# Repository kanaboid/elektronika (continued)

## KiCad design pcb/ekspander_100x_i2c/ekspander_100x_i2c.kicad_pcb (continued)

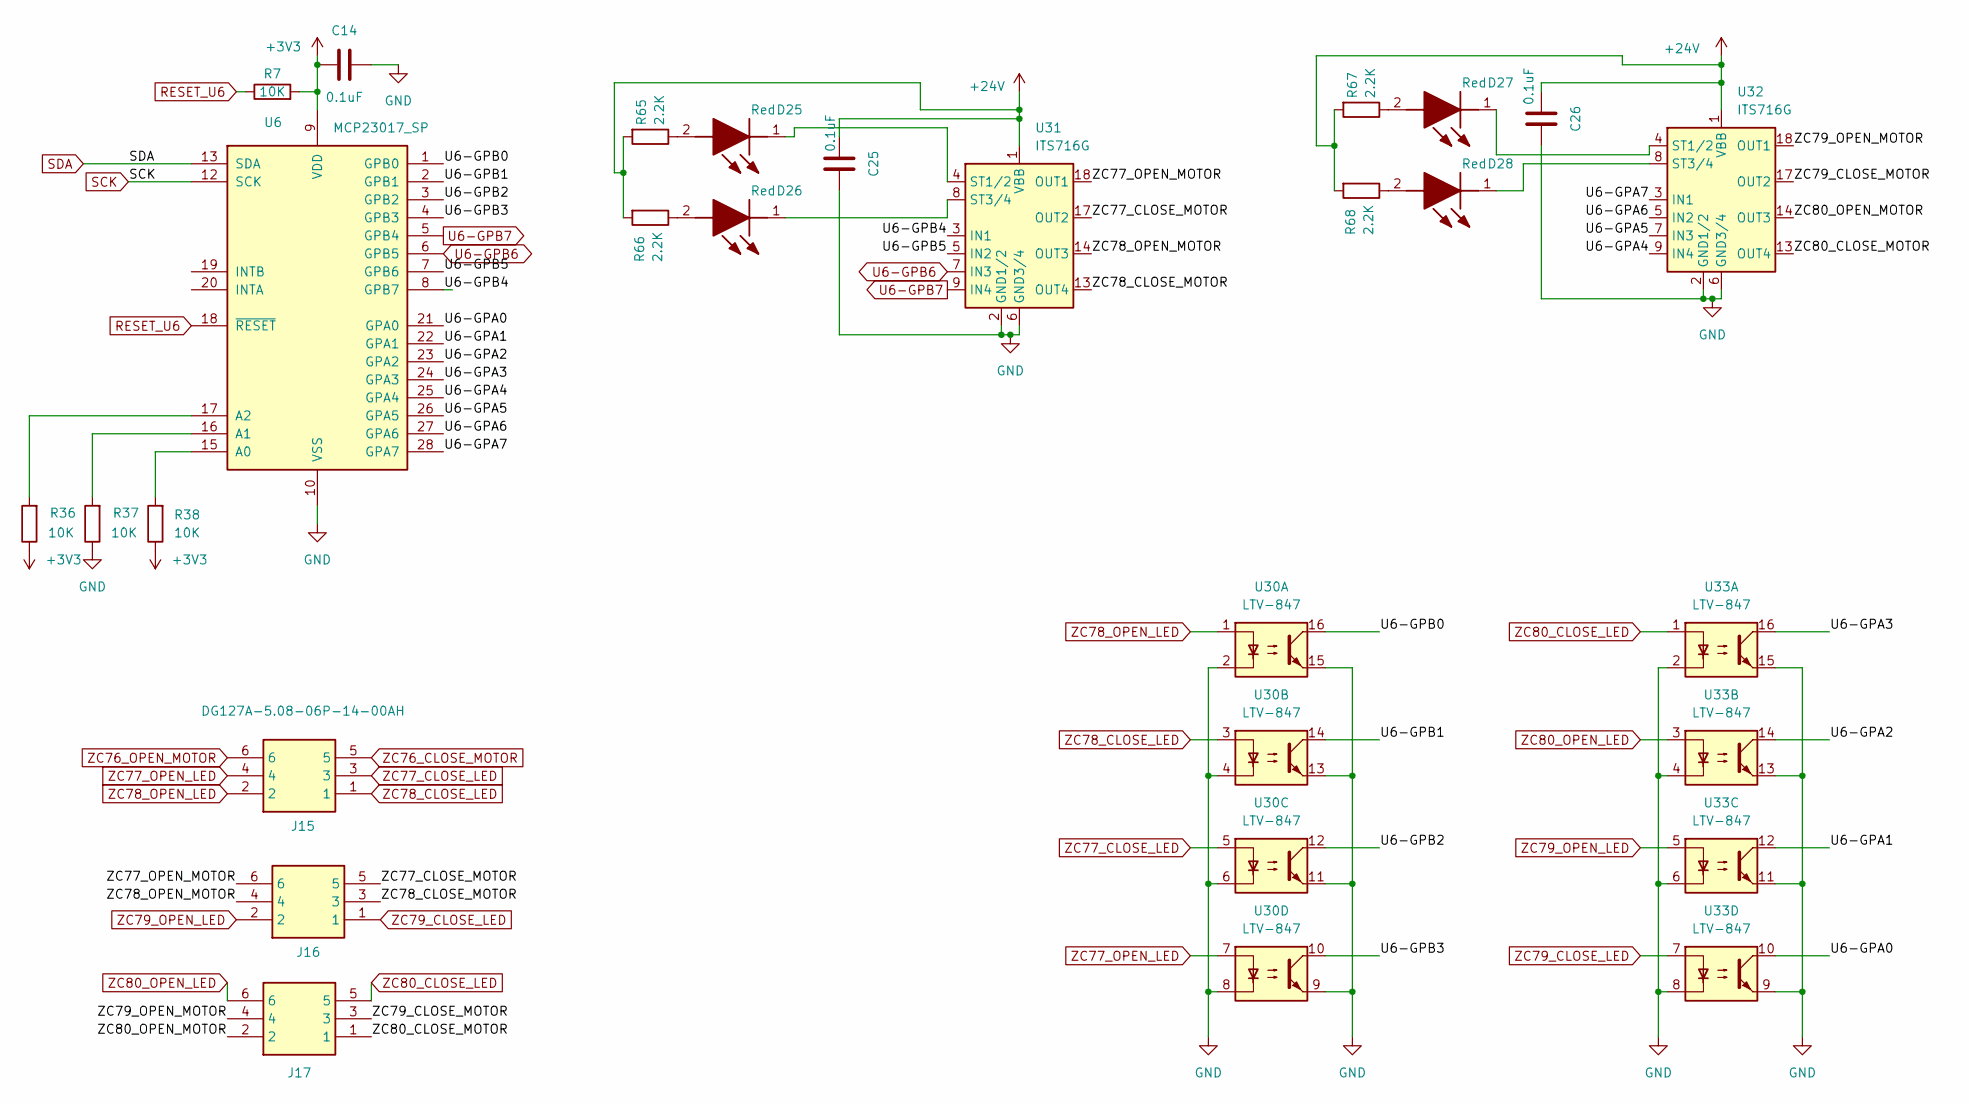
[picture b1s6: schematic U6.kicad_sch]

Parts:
C14, C25, C26: 0.1uF; C_0805_2012Metric_Pad1.18x1.45mm_HandSolder
D25, D26, D27, D28: Red; LEDC2012X120N; Manufacturer_Part_Number LTST-C170KRKT; Mouser Part Number 859-LTST-C170KRKT
J15, J16, J17: DG127A-5.08-06P-14-00AH; DG127A50806P1400AH; Manufacturer_Part_Number DG127A-5.08-06P-14-00AH
R7, R36, R37, R38: 10K; R_0805_2012Metric_Pad1.20x1.40mm_HandSolder
R65, R66, R67, R68: 2.2K; R_0805_2012Metric_Pad1.20x1.40mm_HandSolder
U6: MCP23017_SP; DIP-28_W7.62mm
U30, U33: LTV-847; DIP-16_W7.62mm
U31, U32: ITS716G; SOIC-20W_7.5x12.8mm_P1.27mm

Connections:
+3V3: C14.1, R7.2, R36.1, R38.1, U6.9 (VDD); also elsewhere on the board
+24V: C25.1, C26.1, R65.2, R66.2, R67.2, R68.2, U31.1 (VBB), U31.10 (VBB), U31.11 (VBB), U31.12 (VBB), U31.15 (VBB), U31.16 (VBB), U31.19 (VBB), U31.20 (VBB), U32.1 (VBB), U32.10 (VBB), U32.11 (VBB), U32.12 (VBB), U32.15 (VBB), U32.16 (VBB), U32.19 (VBB), U32.20 (VBB); also elsewhere on the board
/U6/U6-GPA0: U6.21 (GPA0), U33.10
/U6/U6-GPA1: U6.22 (GPA1), U33.12
/U6/U6-GPA2: U6.23 (GPA2), U33.14
/U6/U6-GPA3: U6.24 (GPA3), U33.16
/U6/U6-GPA4: U6.25 (GPA4), U32.9 (IN4)
/U6/U6-GPA5: U6.26 (GPA5), U32.7 (IN3)
/U6/U6-GPA6: U6.27 (GPA6), U32.5 (IN2)
/U6/U6-GPA7: U6.28 (GPA7), U32.3 (IN1)
/U6/U6-GPB0: U6.1 (GPB0), U30.16
/U6/U6-GPB1: U6.2 (GPB1), U30.14
/U6/U6-GPB2: U6.3 (GPB2), U30.12
/U6/U6-GPB3: U6.4 (GPB3), U30.10
/U6/U6-GPB4: U6.8 (GPB7), U31.3 (IN1)
/U6/U6-GPB5: U6.7 (GPB6), U31.5 (IN2)
/U6/ZC77_CLOSE_MOTOR: J16.5, U31.17 (OUT2)
/U6/ZC77_OPEN_MOTOR: J16.6, U31.18 (OUT1)
/U6/ZC78_CLOSE_MOTOR: J16.3, U31.13 (OUT4)
/U6/ZC78_OPEN_MOTOR: J16.4, U31.14 (OUT3)
/U6/ZC79_CLOSE_MOTOR: J17.3, U32.17 (OUT2)
/U6/ZC79_OPEN_MOTOR: J17.4, U32.18 (OUT1)
/U6/ZC80_CLOSE_MOTOR: J17.1, U32.13 (OUT4)
/U6/ZC80_OPEN_MOTOR: J17.2, U32.14 (OUT3)
GND: C14.2, C25.2, C26.2, R37.1, U6.10 (VSS), U30.2, U30.4, U30.6, U30.8, U30.9, U30.11, U30.13, U30.15, U31.2 (GND1/2), U31.6 (GND3/4), U32.2 (GND1/2), U32.6 (GND3/4), U33.2, U33.4, U33.6, U33.8, U33.9, U33.11, U33.13, U33.15; also elsewhere on the board
unnamed: D25.2 (A), R65.1
unnamed: D25.1 (K), U31.4 (ST1/2)
unnamed: D26.2 (A), R66.1
unnamed: D26.1 (K), U31.8 (ST3/4)
unnamed: D27.2 (A), R67.1
unnamed: D27.1 (K), U32.4 (ST1/2)
unnamed: D28.2 (A), R68.1
unnamed: D28.1 (K), U32.8 (ST3/4)
unnamed: R38.2, U6.15 (A0)
unnamed: R37.2, U6.16 (A1)
unnamed: R36.2, U6.17 (A2)
RESET_U6: R7.1, U6.18 (~RESET); also elsewhere on the board
SCK: U6.12 (SCK); also elsewhere on the board
SDA: U6.13 (SDA); also elsewhere on the board
U6-GPB6: U6.6 (GPB5), U31.7 (IN3)
U6-GPB7: U6.5 (GPB4), U31.9 (IN4)
ZC76_CLOSE_MOTOR: J15.5; also elsewhere on the board
ZC76_OPEN_MOTOR: J15.6; also elsewhere on the board
ZC77_CLOSE_LED: J15.3, U30.5
ZC77_OPEN_LED: J15.4, U30.7
ZC78_CLOSE_LED: J15.1, U30.3
ZC78_OPEN_LED: J15.2, U30.1
ZC79_CLOSE_LED: J16.1, U33.7
ZC79_OPEN_LED: J16.2, U33.5
ZC80_CLOSE_LED: J17.5, U33.1
ZC80_OPEN_LED: J17.6, U33.3

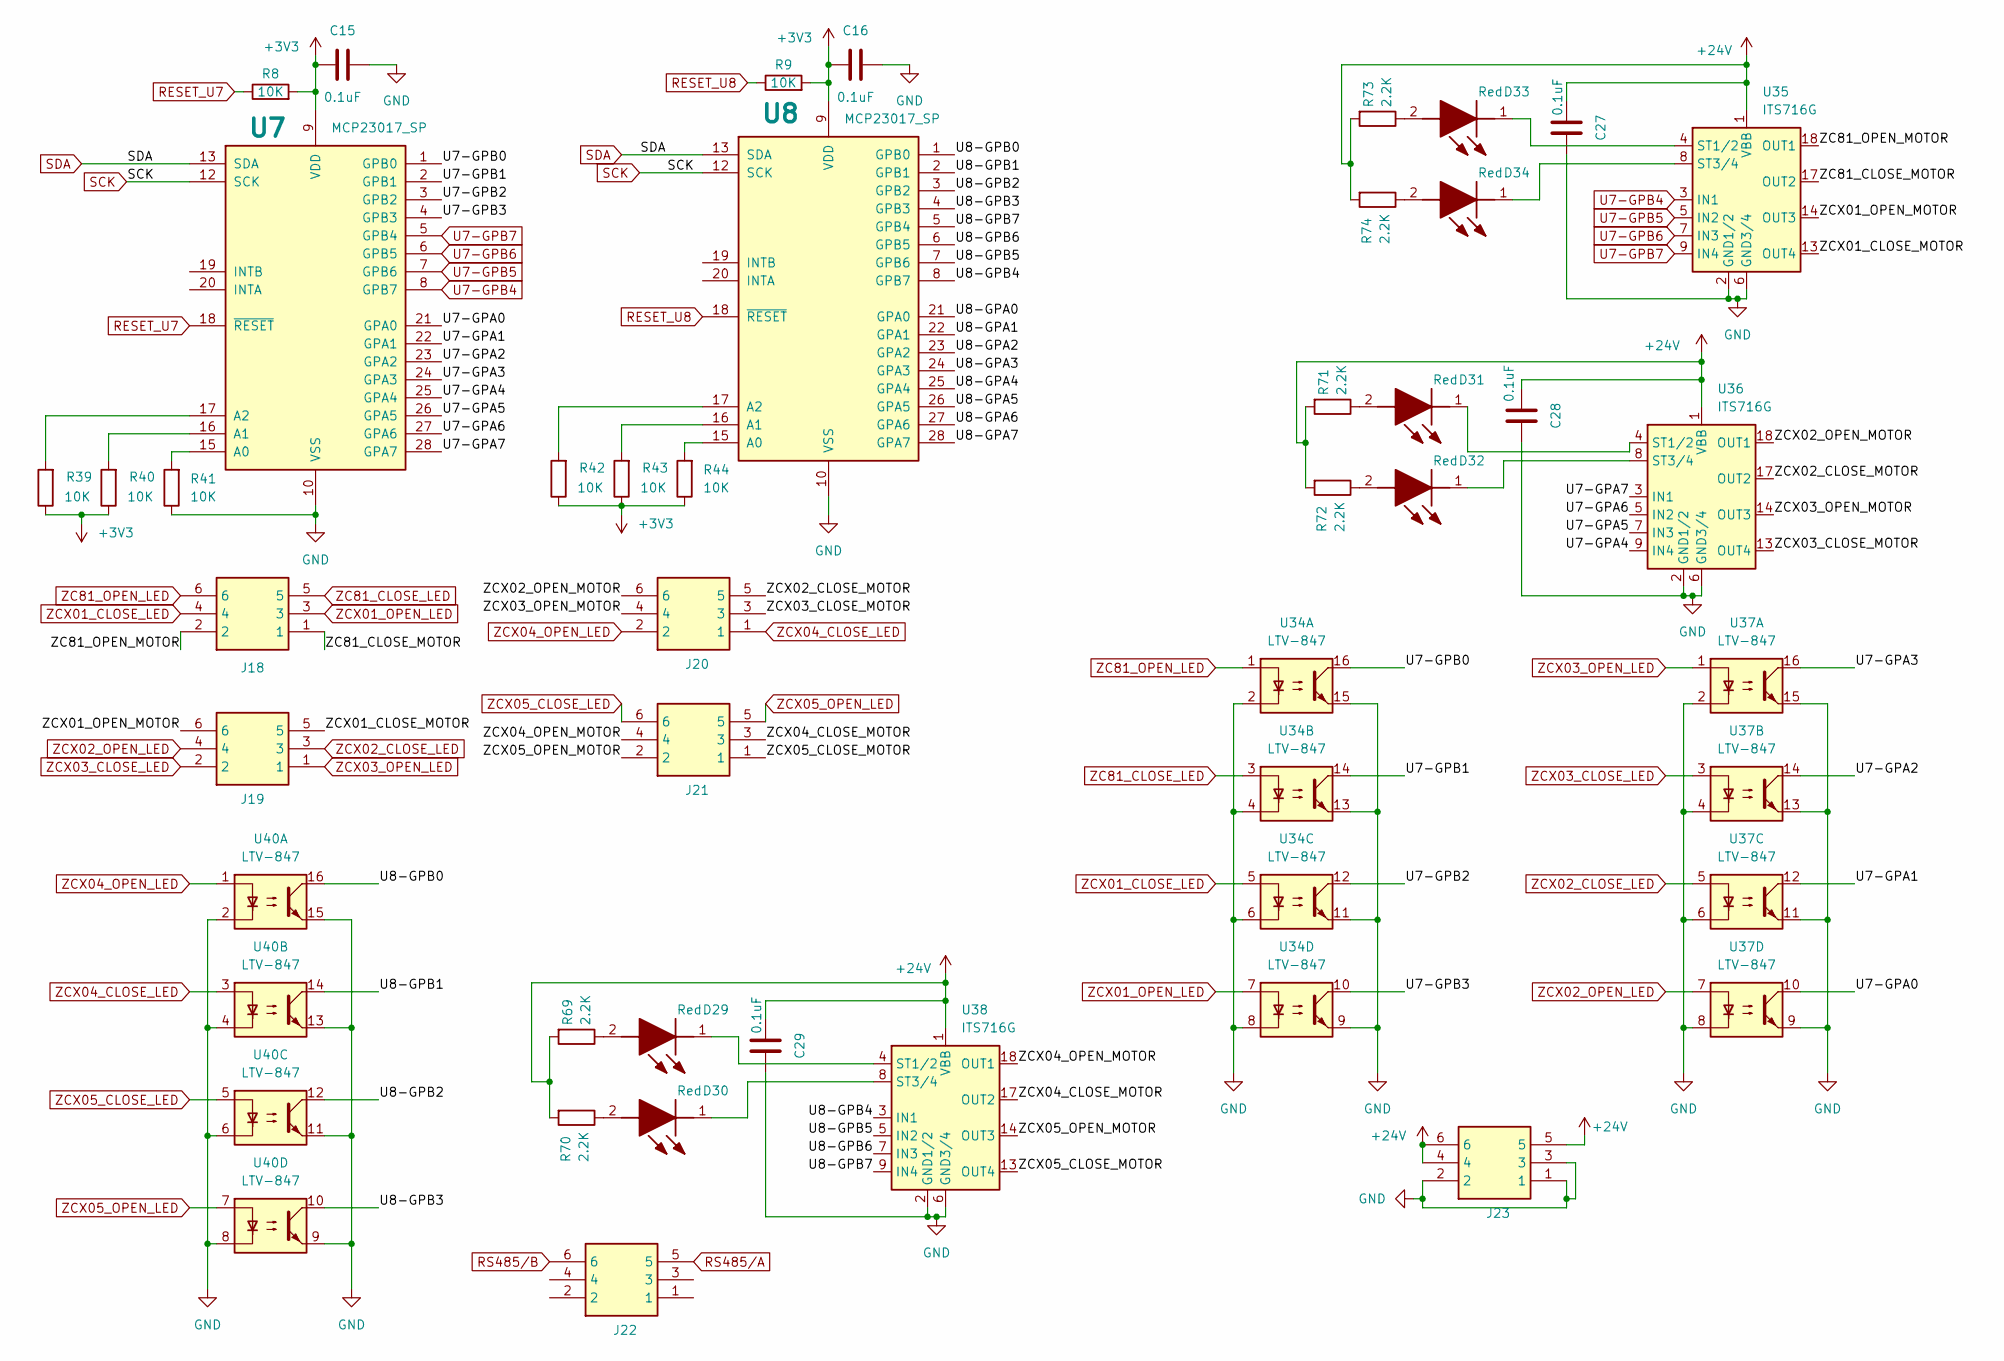
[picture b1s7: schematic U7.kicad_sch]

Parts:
C15, C16, C27, C28, C29: 0.1uF; C_0805_2012Metric_Pad1.18x1.45mm_HandSolder
D29, D30, D31, D32, D33, D34: Red; LEDC2012X120N; Manufacturer_Part_Number LTST-C170KRKT; Mouser Part Number 859-LTST-C170KRKT
J18, J19, J20, J21, J22, J23: DG127A-5.08-06P-14-00AH; DG127A50806P1400AH; Manufacturer_Part_Number DG127A-5.08-06P-14-00AH
R8, R9, R39, R40, R41, R42, R43, R44: 10K; R_0805_2012Metric_Pad1.20x1.40mm_HandSolder
R69, R70, R71, R72, R73, R74: 2.2K; R_0805_2012Metric_Pad1.20x1.40mm_HandSolder
U7, U8: MCP23017_SP; DIP-28_W7.62mm
U34, U37, U40: LTV-847; DIP-16_W7.62mm
U35, U36, U38: ITS716G; SOIC-20W_7.5x12.8mm_P1.27mm

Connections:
+3V3: C15.1, C16.1, R8.2, R9.2, R39.1, R40.1, R42.1, R43.1, R44.1, U7.9 (VDD), U8.9 (VDD); also elsewhere on the board
+24V: C27.1, C28.1, C29.1, J23.4, J23.5, J23.6, R69.2, R70.2, R71.2, R72.2, R73.2, R74.2, U35.1 (VBB), U35.10 (VBB), U35.11 (VBB), U35.12 (VBB), U35.15 (VBB), U35.16 (VBB), U35.19 (VBB), U35.20 (VBB), U36.1 (VBB), U36.10 (VBB), U36.11 (VBB), U36.12 (VBB), U36.15 (VBB), U36.16 (VBB), U36.19 (VBB), U36.20 (VBB), U38.1 (VBB), U38.10 (VBB), U38.11 (VBB), U38.12 (VBB), U38.15 (VBB), U38.16 (VBB), U38.19 (VBB), U38.20 (VBB); also elsewhere on the board
/U7 - U8/U7-GPA0: U7.21 (GPA0), U37.10
/U7 - U8/U7-GPA1: U7.22 (GPA1), U37.12
/U7 - U8/U7-GPA2: U7.23 (GPA2), U37.14
/U7 - U8/U7-GPA3: U7.24 (GPA3), U37.16
/U7 - U8/U7-GPA4: U7.25 (GPA4), U36.9 (IN4)
/U7 - U8/U7-GPA5: U7.26 (GPA5), U36.7 (IN3)
/U7 - U8/U7-GPA6: U7.27 (GPA6), U36.5 (IN2)
/U7 - U8/U7-GPA7: U7.28 (GPA7), U36.3 (IN1)
/U7 - U8/U7-GPB0: U7.1 (GPB0), U34.16
/U7 - U8/U7-GPB1: U7.2 (GPB1), U34.14
/U7 - U8/U7-GPB2: U7.3 (GPB2), U34.12
/U7 - U8/U7-GPB3: U7.4 (GPB3), U34.10
/U7 - U8/U8-GPA0: U8.21 (GPA0)
/U7 - U8/U8-GPA1: U8.22 (GPA1)
/U7 - U8/U8-GPA2: U8.23 (GPA2)
/U7 - U8/U8-GPA3: U8.24 (GPA3)
/U7 - U8/U8-GPA4: U8.25 (GPA4)
/U7 - U8/U8-GPA5: U8.26 (GPA5)
/U7 - U8/U8-GPA6: U8.27 (GPA6)
/U7 - U8/U8-GPA7: U8.28 (GPA7)
/U7 - U8/U8-GPB0: U8.1 (GPB0), U40.16
/U7 - U8/U8-GPB1: U8.2 (GPB1), U40.14
/U7 - U8/U8-GPB2: U8.3 (GPB2), U40.12
/U7 - U8/U8-GPB3: U8.4 (GPB3), U40.10
/U7 - U8/U8-GPB4: U8.8 (GPB7), U38.3 (IN1)
/U7 - U8/U8-GPB5: U8.7 (GPB6), U38.5 (IN2)
/U7 - U8/U8-GPB6: U8.6 (GPB5), U38.7 (IN3)
/U7 - U8/U8-GPB7: U8.5 (GPB4), U38.9 (IN4)
/U7 - U8/ZC81_CLOSE_MOTOR: J18.1, U35.17 (OUT2)
/U7 - U8/ZC81_OPEN_MOTOR: J18.2, U35.18 (OUT1)
/U7 - U8/ZCX01_CLOSE_MOTOR: J19.5, U35.13 (OUT4)
/U7 - U8/ZCX01_OPEN_MOTOR: J19.6, U35.14 (OUT3)
/U7 - U8/ZCX02_CLOSE_MOTOR: J20.5, U36.17 (OUT2)
/U7 - U8/ZCX02_OPEN_MOTOR: J20.6, U36.18 (OUT1)
/U7 - U8/ZCX03_CLOSE_MOTOR: J20.3, U36.13 (OUT4)
/U7 - U8/ZCX03_OPEN_MOTOR: J20.4, U36.14 (OUT3)
/U7 - U8/ZCX04_CLOSE_MOTOR: J21.3, U38.17 (OUT2)
/U7 - U8/ZCX04_OPEN_MOTOR: J21.4, U38.18 (OUT1)
/U7 - U8/ZCX05_CLOSE_MOTOR: J21.1, U38.13 (OUT4)
/U7 - U8/ZCX05_OPEN_MOTOR: J21.2, U38.14 (OUT3)
GND: C15.2, C16.2, C27.2, C28.2, C29.2, J23.1, J23.2, J23.3, R41.1, U7.10 (VSS), U8.10 (VSS), U34.2, U34.4, U34.6, U34.8, U34.9, U34.11, U34.13, U34.15, U35.2 (GND1/2), U35.6 (GND3/4), U36.2 (GND1/2), U36.6 (GND3/4), U37.2, U37.4, U37.6, U37.8, U37.9, U37.11, U37.13, U37.15, U38.2 (GND1/2), U38.6 (GND3/4), U40.2, U40.4, U40.6, U40.8, U40.9, U40.11, U40.13, U40.15; also elsewhere on the board
unnamed: D29.2 (A), R69.1
unnamed: D29.1 (K), U38.4 (ST1/2)
unnamed: D30.2 (A), R70.1
unnamed: D30.1 (K), U38.8 (ST3/4)
unnamed: D31.2 (A), R71.1
unnamed: D31.1 (K), U36.4 (ST1/2)
unnamed: D32.2 (A), R72.1
unnamed: D32.1 (K), U36.8 (ST3/4)
unnamed: D33.2 (A), R73.1
unnamed: D33.1 (K), U35.4 (ST1/2)
unnamed: D34.2 (A), R74.1
unnamed: D34.1 (K), U35.8 (ST3/4)
unnamed: R41.2, U7.15 (A0)
unnamed: R40.2, U7.16 (A1)
unnamed: R39.2, U7.17 (A2)
unnamed: R44.2, U8.15 (A0)
unnamed: R43.2, U8.16 (A1)
unnamed: R42.2, U8.17 (A2)
RESET_U7: R8.1, U7.18 (~RESET); also elsewhere on the board
RESET_U8: R9.1, U8.18 (~RESET); also elsewhere on the board
RS485/A: J22.5; also elsewhere on the board
RS485/B: J22.6; also elsewhere on the board
SCK: U7.12 (SCK), U8.12 (SCK); also elsewhere on the board
SDA: U7.13 (SDA), U8.13 (SDA); also elsewhere on the board
U7-GPB4: U7.8 (GPB7), U35.3 (IN1)
U7-GPB5: U7.7 (GPB6), U35.5 (IN2)
U7-GPB6: U7.6 (GPB5), U35.7 (IN3)
U7-GPB7: U7.5 (GPB4), U35.9 (IN4)
ZC81_CLOSE_LED: J18.5, U34.3
ZC81_OPEN_LED: J18.6, U34.1
ZCX01_CLOSE_LED: J18.4, U34.5
ZCX01_OPEN_LED: J18.3, U34.7
ZCX02_CLOSE_LED: J19.3, U37.5
ZCX02_OPEN_LED: J19.4, U37.7
ZCX03_CLOSE_LED: J19.2, U37.3
ZCX03_OPEN_LED: J19.1, U37.1
ZCX04_CLOSE_LED: J20.1, U40.3
ZCX04_OPEN_LED: J20.2, U40.1
ZCX05_CLOSE_LED: J21.6, U40.5
ZCX05_OPEN_LED: J21.5, U40.7

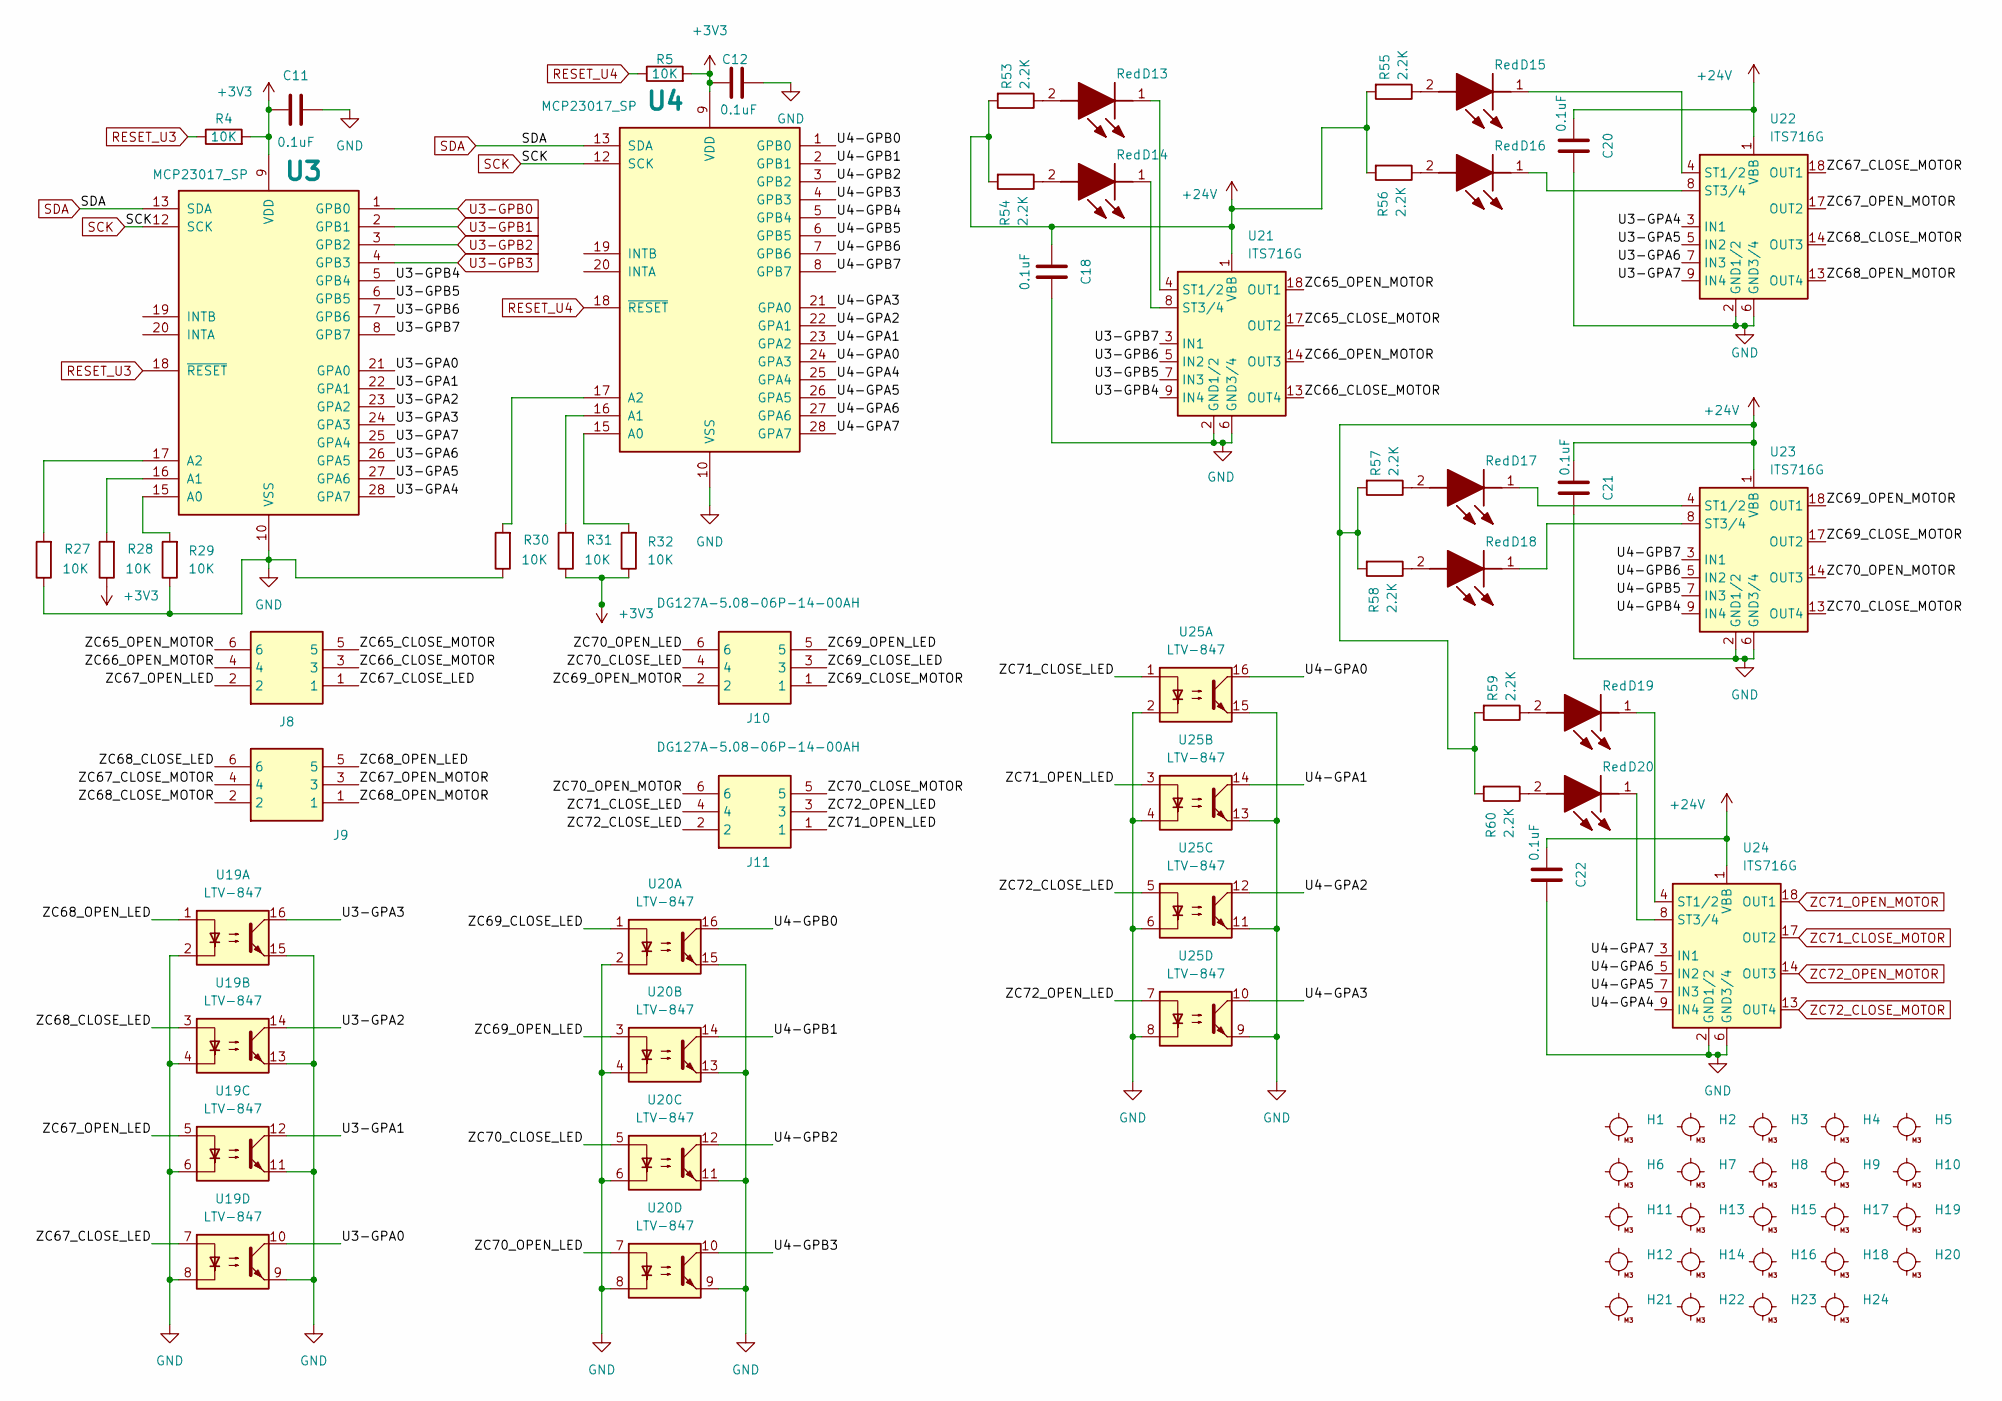
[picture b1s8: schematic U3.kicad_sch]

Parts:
C11, C12, C18, C20, C21, C22: 0.1uF; C_0805_2012Metric_Pad1.18x1.45mm_HandSolder
D13, D14, D15, D16, D17, D18, D19, D20: Red; LEDC2012X120N; Manufacturer_Part_Number LTST-C170KRKT; Mouser Part Number 859-LTST-C170KRKT
H1, H2, H3, H4, H5, H6, H7, H8, H9, H10, H11, H12, H13, H14, H15, H16, H17, H18, H19, H20, H21, H22, H23, H24: MountingHole_M3
J8, J9, J10, J11: DG127A-5.08-06P-14-00AH; DG127A50806P1400AH; Manufacturer_Part_Number DG127A-5.08-06P-14-00AH
R4, R5, R27, R28, R29, R30, R31, R32: 10K; R_0805_2012Metric_Pad1.20x1.40mm_HandSolder
R53, R54, R55, R56, R57, R58, R59, R60: 2.2K; R_0805_2012Metric_Pad1.20x1.40mm_HandSolder
U3, U4: MCP23017_SP; DIP-28_W7.62mm
U19, U20, U25: LTV-847; DIP-16_W7.62mm
U21, U22, U23, U24: ITS716G; SOIC-20W_7.5x12.8mm_P1.27mm

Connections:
+3V3: C11.1, C12.1, R4.2, R5.2, R28.1, R31.1, R32.1, U3.9 (VDD), U4.9 (VDD); also elsewhere on the board
+24V: C18.1, C20.1, C21.1, C22.1, R53.2, R54.2, R55.2, R56.2, R57.2, R58.2, R59.2, R60.2, U21.1 (VBB), U21.10 (VBB), U21.11 (VBB), U21.12 (VBB), U21.15 (VBB), U21.16 (VBB), U21.19 (VBB), U21.20 (VBB), U22.1 (VBB), U22.10 (VBB), U22.11 (VBB), U22.12 (VBB), U22.15 (VBB), U22.16 (VBB), U22.19 (VBB), U22.20 (VBB), U23.1 (VBB), U23.10 (VBB), U23.11 (VBB), U23.12 (VBB), U23.15 (VBB), U23.16 (VBB), U23.19 (VBB), U23.20 (VBB), U24.1 (VBB), U24.10 (VBB), U24.11 (VBB), U24.12 (VBB), U24.15 (VBB), U24.16 (VBB), U24.19 (VBB), U24.20 (VBB); also elsewhere on the board
/U3 - U4/U3-GPA0: U3.21 (GPA0), U19.10
/U3 - U4/U3-GPA1: U3.22 (GPA1), U19.12
/U3 - U4/U3-GPA2: U3.23 (GPA2), U19.14
/U3 - U4/U3-GPA3: U3.24 (GPA3), U19.16
/U3 - U4/U3-GPA4: U3.28 (GPA7), U22.3 (IN1)
/U3 - U4/U3-GPA5: U3.27 (GPA6), U22.5 (IN2)
/U3 - U4/U3-GPA6: U3.26 (GPA5), U22.7 (IN3)
/U3 - U4/U3-GPA7: U3.25 (GPA4), U22.9 (IN4)
/U3 - U4/U3-GPB4: U3.5 (GPB4), U21.9 (IN4)
/U3 - U4/U3-GPB5: U3.6 (GPB5), U21.7 (IN3)
/U3 - U4/U3-GPB6: U3.7 (GPB6), U21.5 (IN2)
/U3 - U4/U3-GPB7: U3.8 (GPB7), U21.3 (IN1)
/U3 - U4/U4-GPA0: U4.24 (GPA3), U25.16
/U3 - U4/U4-GPA1: U4.23 (GPA2), U25.14
/U3 - U4/U4-GPA2: U4.22 (GPA1), U25.12
/U3 - U4/U4-GPA3: U4.21 (GPA0), U25.10
/U3 - U4/U4-GPA4: U4.25 (GPA4), U24.9 (IN4)
/U3 - U4/U4-GPA5: U4.26 (GPA5), U24.7 (IN3)
/U3 - U4/U4-GPA6: U4.27 (GPA6), U24.5 (IN2)
/U3 - U4/U4-GPA7: U4.28 (GPA7), U24.3 (IN1)
/U3 - U4/U4-GPB0: U4.1 (GPB0), U20.16
/U3 - U4/U4-GPB1: U4.2 (GPB1), U20.14
/U3 - U4/U4-GPB2: U4.3 (GPB2), U20.12
/U3 - U4/U4-GPB3: U4.4 (GPB3), U20.10
/U3 - U4/U4-GPB4: U4.5 (GPB4), U23.9 (IN4)
/U3 - U4/U4-GPB5: U4.6 (GPB5), U23.7 (IN3)
/U3 - U4/U4-GPB6: U4.7 (GPB6), U23.5 (IN2)
/U3 - U4/U4-GPB7: U4.8 (GPB7), U23.3 (IN1)
/U3 - U4/ZC65_CLOSE_MOTOR: J8.5, U21.17 (OUT2)
/U3 - U4/ZC65_OPEN_MOTOR: J8.6, U21.18 (OUT1)
/U3 - U4/ZC66_CLOSE_MOTOR: J8.3, U21.13 (OUT4)
/U3 - U4/ZC66_OPEN_MOTOR: J8.4, U21.14 (OUT3)
/U3 - U4/ZC67_CLOSE_LED: J8.1, U19.7
/U3 - U4/ZC67_CLOSE_MOTOR: J9.4, U22.18 (OUT1)
/U3 - U4/ZC67_OPEN_LED: J8.2, U19.5
/U3 - U4/ZC67_OPEN_MOTOR: J9.3, U22.17 (OUT2)
/U3 - U4/ZC68_CLOSE_LED: J9.6, U19.3
/U3 - U4/ZC68_CLOSE_MOTOR: J9.2, U22.14 (OUT3)
/U3 - U4/ZC68_OPEN_LED: J9.5, U19.1
/U3 - U4/ZC68_OPEN_MOTOR: J9.1, U22.13 (OUT4)
/U3 - U4/ZC69_CLOSE_LED: J10.3, U20.1
/U3 - U4/ZC69_CLOSE_MOTOR: J10.1, U23.17 (OUT2)
/U3 - U4/ZC69_OPEN_LED: J10.5, U20.3
/U3 - U4/ZC69_OPEN_MOTOR: J10.2, U23.18 (OUT1)
/U3 - U4/ZC70_CLOSE_LED: J10.4, U20.5
/U3 - U4/ZC70_CLOSE_MOTOR: J11.5, U23.13 (OUT4)
/U3 - U4/ZC70_OPEN_LED: J10.6, U20.7
/U3 - U4/ZC70_OPEN_MOTOR: J11.6, U23.14 (OUT3)
/U3 - U4/ZC71_CLOSE_LED: J11.4, U25.1
/U3 - U4/ZC71_OPEN_LED: J11.1, U25.3
/U3 - U4/ZC72_CLOSE_LED: J11.2, U25.5
/U3 - U4/ZC72_OPEN_LED: J11.3, U25.7
GND: C11.2, C12.2, C18.2, C20.2, C21.2, C22.2, R27.1, R29.1, R30.1, U3.10 (VSS), U4.10 (VSS), U19.2, U19.4, U19.6, U19.8, U19.9, U19.11, U19.13, U19.15, U20.2, U20.4, U20.6, U20.8, U20.9, U20.11, U20.13, U20.15, U21.2 (GND1/2), U21.6 (GND3/4), U22.2 (GND1/2), U22.6 (GND3/4), U23.2 (GND1/2), U23.6 (GND3/4), U24.2 (GND1/2), U24.6 (GND3/4), U25.2, U25.4, U25.6, U25.8, U25.9, U25.11, U25.13, U25.15; also elsewhere on the board
unnamed: D13.2 (A), R53.1
unnamed: D13.1 (K), U21.4 (ST1/2)
unnamed: D14.2 (A), R54.1
unnamed: D14.1 (K), U21.8 (ST3/4)
unnamed: D15.2 (A), R55.1
unnamed: D15.1 (K), U22.4 (ST1/2)
unnamed: D16.2 (A), R56.1
unnamed: D16.1 (K), U22.8 (ST3/4)
unnamed: D17.2 (A), R57.1
unnamed: D17.1 (K), U23.4 (ST1/2)
unnamed: D18.2 (A), R58.1
unnamed: D18.1 (K), U23.8 (ST3/4)
unnamed: D19.2 (A), R59.1
unnamed: D19.1 (K), U24.4 (ST1/2)
unnamed: D20.2 (A), R60.1
unnamed: D20.1 (K), U24.8 (ST3/4)
unnamed: R29.2, U3.15 (A0)
unnamed: R28.2, U3.16 (A1)
unnamed: R27.2, U3.17 (A2)
unnamed: R32.2, U4.15 (A0)
unnamed: R31.2, U4.16 (A1)
unnamed: R30.2, U4.17 (A2)
RESET_U3: R4.1, U3.18 (~RESET); also elsewhere on the board
RESET_U4: R5.1, U4.18 (~RESET); also elsewhere on the board
SCK: U3.12 (SCK), U4.12 (SCK); also elsewhere on the board
SDA: U3.13 (SDA), U4.13 (SDA); also elsewhere on the board
U3-GPB0: U3.1 (GPB0); also elsewhere on the board
U3-GPB1: U3.2 (GPB1); also elsewhere on the board
U3-GPB2: U3.3 (GPB2); also elsewhere on the board
U3-GPB3: U3.4 (GPB3); also elsewhere on the board
ZC71_CLOSE_MOTOR: U24.17 (OUT2); also elsewhere on the board
ZC71_OPEN_MOTOR: U24.18 (OUT1); also elsewhere on the board
ZC72_CLOSE_MOTOR: U24.13 (OUT4); also elsewhere on the board
ZC72_OPEN_MOTOR: U24.14 (OUT3); also elsewhere on the board

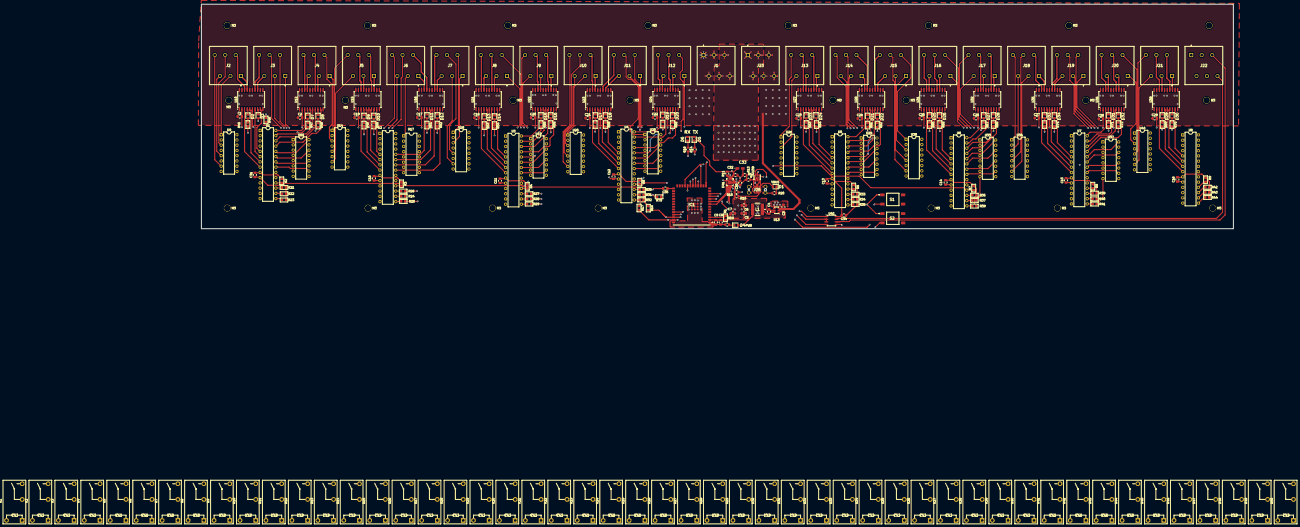
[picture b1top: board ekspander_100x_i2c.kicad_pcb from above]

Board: 4 copper layers, 500.0 x 108.8 mm, 288 parts (0 on the bottom side), 365 nets.

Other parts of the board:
C35: 0.1uF; C_0805_2012Metric_Pad1.18x1.45mm_HandSolder
R75: 10K; R_0805_2012Metric_Pad1.20x1.40mm_HandSolder
S1, S2: 1301.9315; 13019319

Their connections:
+3V3: R75.2; also elsewhere on the board
GND: C35.2, S1.1 (NO_1), S1.2 (NO_2), S2.1 (NO_1), S2.2 (NO_2); also elsewhere on the board
unnamed 282: S2.3 (COM_1), S2.4 (COM_2); also elsewhere on the board
unnamed 283: C35.1, R75.1, S1.3 (COM_1), S1.4 (COM_2); also elsewhere on the board

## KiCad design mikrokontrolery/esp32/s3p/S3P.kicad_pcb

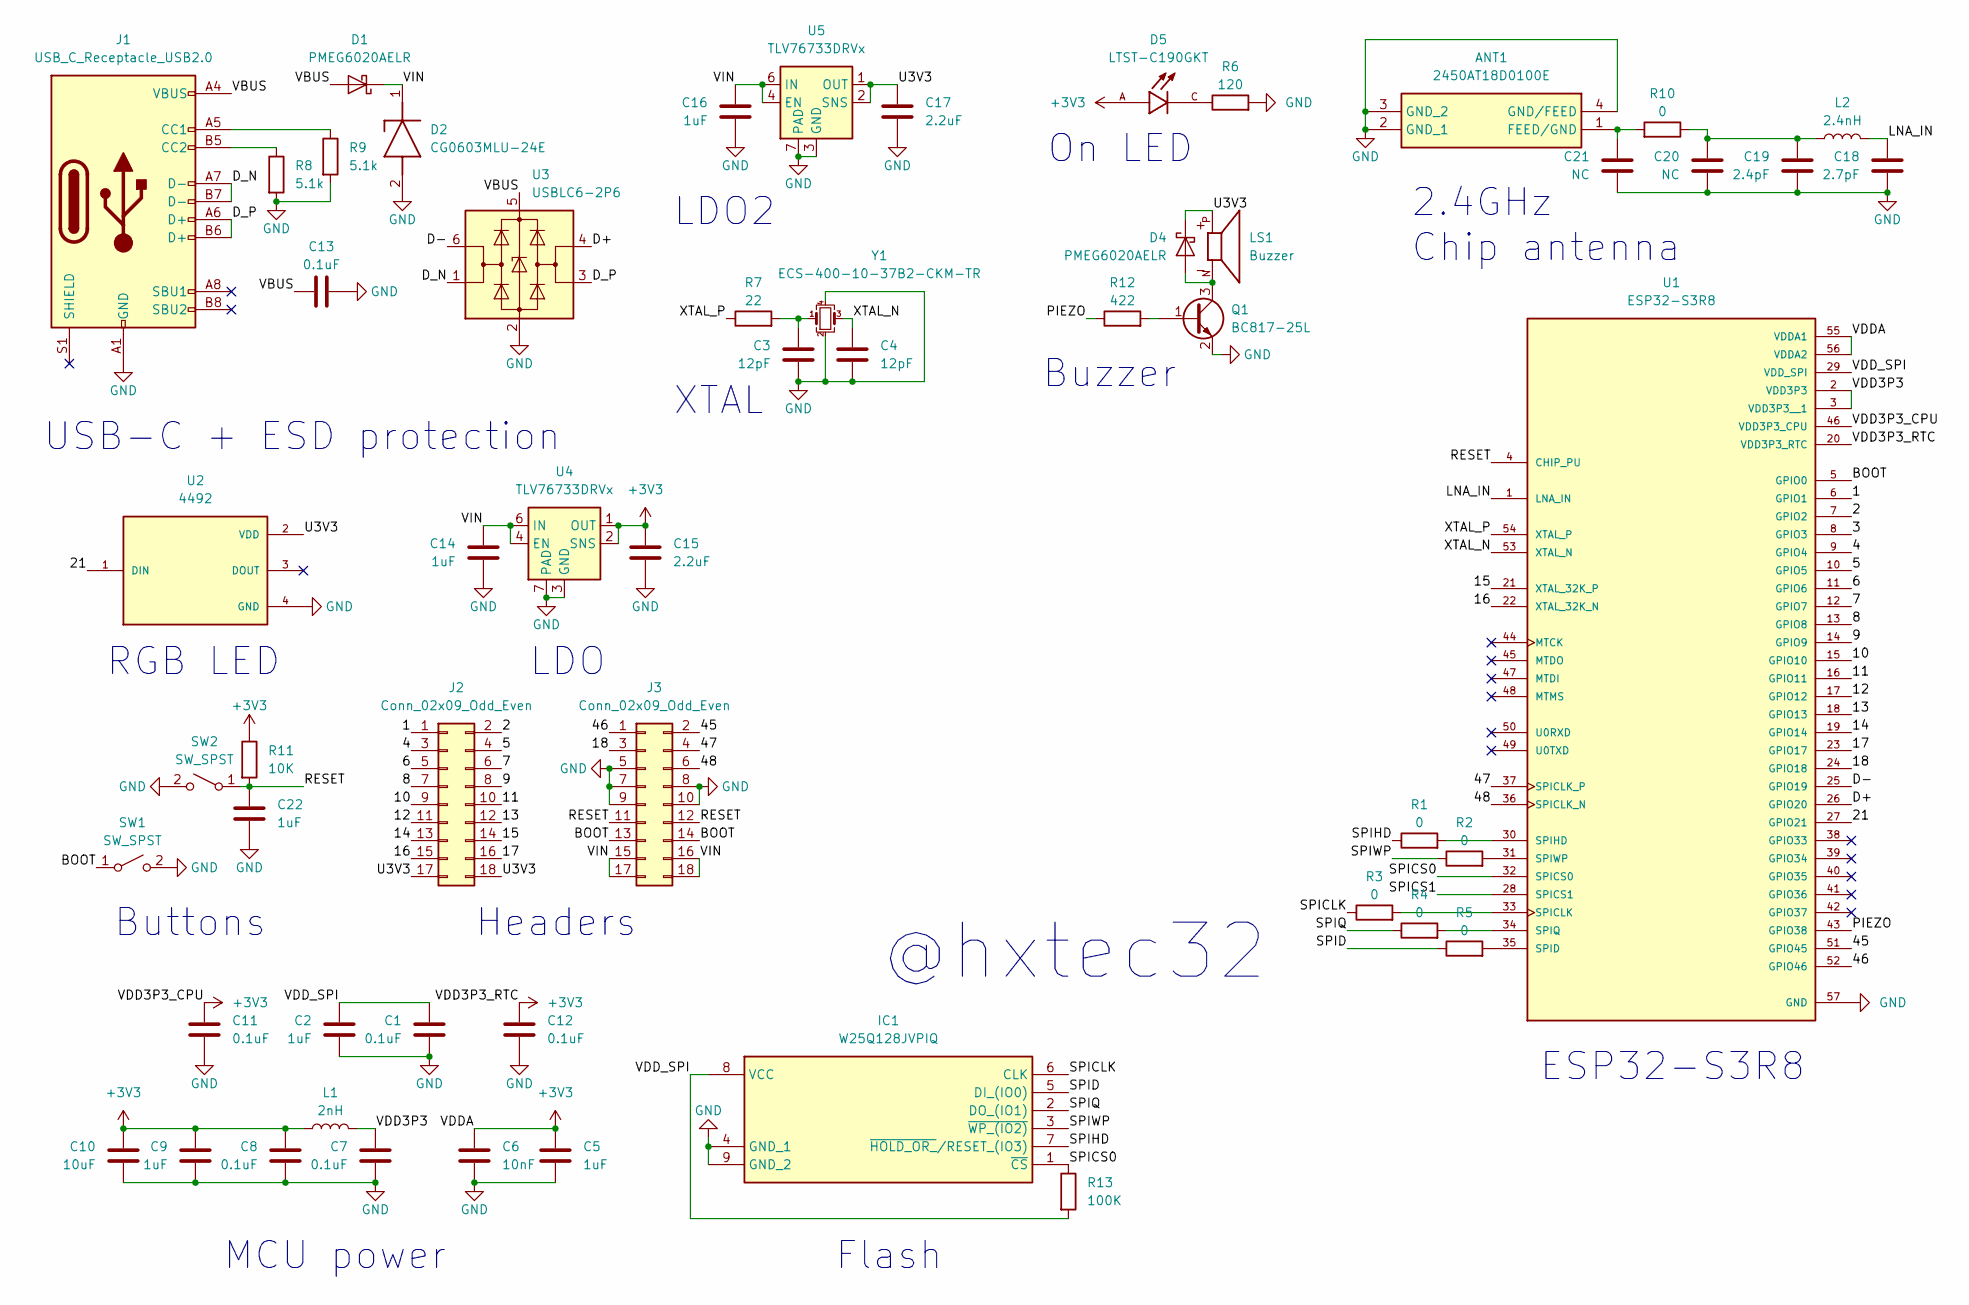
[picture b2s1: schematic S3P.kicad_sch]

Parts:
ANT1: 2450AT18D0100E; Manufacturer_Part_Number 2450AT18D0100E; Mouser Part Number 609-2450AT18D0100E
C1, C7, C8, C11, C12, C13: 0.1uF; R_0402_1005Metric
C2, C5, C9, C22: 1uF; R_0402_1005Metric
C3, C4: 12pF; R_0201_0603Metric
C6: 10nF; R_0201_0603Metric
C10: 10uF; R_0603_1608Metric
C14, C16: 1uF; R_0603_1608Metric
C15, C17: 2.2uF; R_0402_1005Metric
C18: 2.7pF; R_0201_0603Metric
C19: 2.4pF; R_0201_0603Metric
C20, C21: NC; R_0201_0603Metric
D1, D4: PMEG6020AELR; Nexperia_CFP3_SOD-123W
D2: CG0603MLU-24E; DIONC1608X55N; Manufacturer_Part_Number CG0603MLU-24E; Mouser Part Number 652-CG0603MLU-24E
D5: LTST-C190GKT; LEDC1608X35N
IC1: W25Q128JVPIQ; SON127P600X500X80-9N-D; Manufacturer_Part_Number W25Q128JVPIQ; Mouser Part Number 454-W25Q128JVPIQ
J1: USB_C_Receptacle_USB2.0; USB_C_Receptacle_GCT_USB4105-xx-A_16P_TopMnt_Horizontal
J2, J3: Conn_02x09_Odd_Even; PinHeader_2x09_P2.54mm_Vertical
L1: 2nH; L_0402_1005Metric
L2: 2.4nH; L_0201_0603Metric
LS1: Buzzer; XDCR_CMT-0525-75-SMT-TR; PARTREV 1.0
Q1: BC817-25L; SOT-23
R1, R2, R3, R4, R5, R10: 0; R_0201_0603Metric
R6: 120; R_0402_1005Metric
R7: 22; R_0402_1005Metric
R8, R9: 5.1k; R_0402_1005Metric
R11: 10K; R_0402_1005Metric
R12: 422; R_0402_1005Metric
R13: 100K; R_0201_0603Metric
SW1, SW2: SW_SPST; SW_SPST_PTS810
U1: ESP32-S3R8; QFN40P700X700X90-57N-D
U2: 4492; SK6805-EC15; PARTREV 14/10/19
U3: USBLC6-2P6; SOT-666
U4, U5: TLV76733DRVx; WSON-6-1EP_2x2mm_P0.65mm_EP1x1.6mm_ThermalVias
Y1: ECS-400-10-37B2-CKM-TR; Crystal_SMD_2016-4Pin_2.0x1.6mm

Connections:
+3V3: C5.1, C6.1, C8.1, C9.1, C10.1, C11.1, C12.1, C15.1, D5.A, L1.2, R11.1, U1.20 (VDD3P3_RTC), U1.46 (VDD3P3_CPU), U1.55 (VDDA1), U1.56 (VDDA2), U4.1 (OUT), U4.2 (SNS)
/1: J2.1, U1.6 (GPIO1)
/2: J2.2, U1.7 (GPIO2)
/3: U1.8 (GPIO3)
/4: J2.3, U1.9 (GPIO4)
/5: J2.4, U1.10 (GPIO5)
/6: J2.5, U1.11 (GPIO6)
/7: J2.6, U1.12 (GPIO7)
/8: J2.7, U1.13 (GPIO8)
/9: J2.8, U1.14 (GPIO9)
/10: J2.9, U1.15 (GPIO10)
/11: J2.10, U1.16 (GPIO11)
/12: J2.11, U1.17 (GPIO12)
/13: J2.12, U1.18 (GPIO13)
/14: J2.13, U1.19 (GPIO14)
/15: J2.14, U1.21 (XTAL_32K_P)
/16: J2.15, U1.22 (XTAL_32K_N)
/17: J2.16, U1.23 (GPIO17)
/18: J3.3, U1.24 (GPIO18)
/21: U1.27 (GPIO21), U2.1 (DIN)
/45: J3.2, U1.51 (GPIO45)
/46: J3.1, U1.52 (GPIO46)
/47: J3.4, U1.37 (SPICLK_P)
/48: J3.6, U1.36 (SPICLK_N)
/BOOT: J3.13, J3.14, SW1.1 (A), U1.5 (GPIO0)
/D+: U1.26 (GPIO20), U3.4 (I/O2)
/D-: U1.25 (GPIO19), U3.6 (I/O1)
/D_N: J1.A7 (D-), J1.B7 (D-), U3.1 (I/O1)
/D_P: J1.A6 (D+), J1.B6 (D+), U3.3 (I/O2)
/LNA_IN: C18.1, L2.1, U1.1 (LNA_IN)
/PIEZO: R12.1, U1.43 (GPIO38)
/RESET: C22.1, J3.11, J3.12, R11.2, SW2.1 (A), U1.4 (CHIP_PU)
/SPICLK: IC1.6 (CLK), R3.1
/SPICS0: IC1.1 (~CS), R13.1, U1.32 (SPICS0)
/SPICS1: U1.28 (SPICS1)
/SPID: IC1.5 (DI_(IO0)), R5.1
/SPIHD: IC1.7 (~HOLD_OR_/RESET_(IO3)), R1.1
/SPIQ: IC1.2 (DO_(IO1)), R4.1
/SPIWP: IC1.3 (~WP_(IO2)), R2.1
/U3V3: C17.1, D4.1 (K), J2.17, J2.18, LS1.P, U2.2 (VDD), U5.1 (OUT), U5.2 (SNS)
/VBUS: C13.1, D1.2 (A), J1.A4 (VBUS), J1.A9 (VBUS), J1.B4 (VBUS), J1.B9 (VBUS), U3.5 (VBUS)
/VDD3P3: C7.1, L1.1, U1.2 (VDD3P3), U1.3 (VDD3P3__1)
/VDD_SPI: C1.1, C2.1, IC1.8 (VCC), R13.2, U1.29 (VDD_SPI)
/VIN: C14.1, C16.1, D1.1 (K), D2.1 (K), J3.15, J3.16, J3.17, J3.18, U4.4 (EN), U4.6 (IN), U5.4 (EN), U5.6 (IN)
/XTAL_N: C4.1, U1.53 (XTAL_N), Y1.3
/XTAL_P: R7.1, U1.54 (XTAL_P)
GND: ANT1.2 (GND_1), ANT1.3 (GND_2), ANT1.4 (GND/FEED), C1.2, C2.2, C3.2, C4.2, C5.2, C6.2, C7.2, C8.2, C9.2, C10.2, C11.2, C12.2, C13.2, C14.2, C15.2, C16.2, C17.2, C18.2, C19.2, C20.2, C21.2, C22.2, D2.2 (A), IC1.4 (GND_1), IC1.9 (GND_2), J1.A1 (GND), J1.A12 (GND), J1.B1 (GND), J1.B12 (GND), J3.5, J3.7, J3.8, J3.9, J3.10, Q1.2 (E), R6.2, R8.2, R9.2, SW1.2 (B), SW2.2 (B), U1.57 (GND), U2.4 (GND), U3.2 (GND), U4.3 (GND), U4.5 (GND), U4.7 (PAD), U5.3 (GND), U5.5 (GND), U5.7 (PAD), Y1.2, Y1.4
unnamed: ANT1.1 (FEED/GND), C21.1, R10.2
unnamed: C3.1, R7.2, Y1.1
unnamed: C19.1, C20.1, L2.2, R10.1
unnamed: D4.2 (A), LS1.N, Q1.3 (C)
unnamed: D5.C, R6.1
unnamed: J1.A5 (CC1), R9.1
unnamed: J1.B5 (CC2), R8.1
unnamed: Q1.1 (B), R12.2
unnamed: R3.2, U1.33 (SPICLK)
unnamed: R5.2, U1.35 (SPID)
unnamed: R1.2, U1.30 (SPIHD)
unnamed: R4.2, U1.34 (SPIQ)
unnamed: R2.2, U1.31 (SPIWP)

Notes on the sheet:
LDO
Buzzer
Buttons
RGB LED
Flash
USB-C + ESD protection
Chip antenna
Headers
XTAL
@hxtec32
MCU power
On LED
2.4GHz
ESP32-S3R8
LDO2

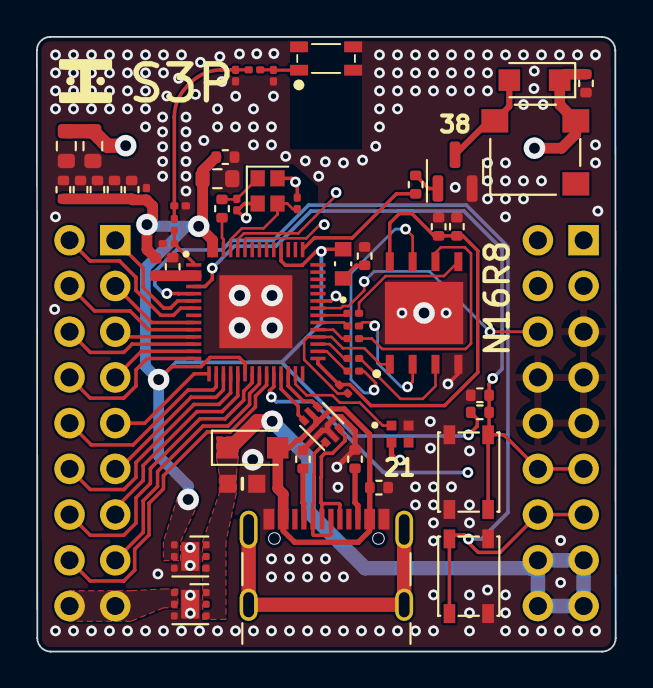
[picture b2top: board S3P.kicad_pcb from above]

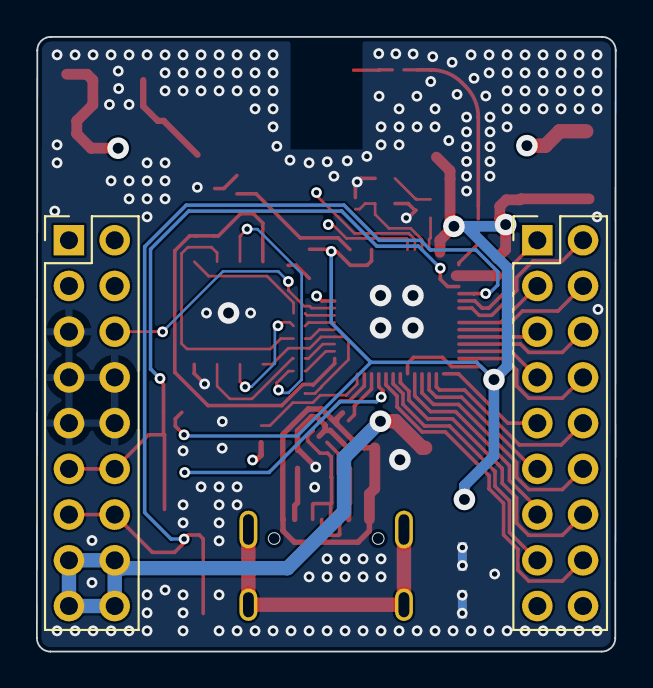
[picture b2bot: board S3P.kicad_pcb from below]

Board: 4 copper layers, 32.2 x 34.1 mm, 56 parts (2 on the bottom side), 58 nets.
